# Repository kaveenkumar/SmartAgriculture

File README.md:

# SmartAgriculture
Bachelor’s final year project, 2014.

## Control of waterflow to irrigation lands from a central system using wireless communication.
Currently deployed at the institute, BMS College of Engineering, Bangalore

### Reference
https://www.researchgate.net/project/Smart-Agriculture-13

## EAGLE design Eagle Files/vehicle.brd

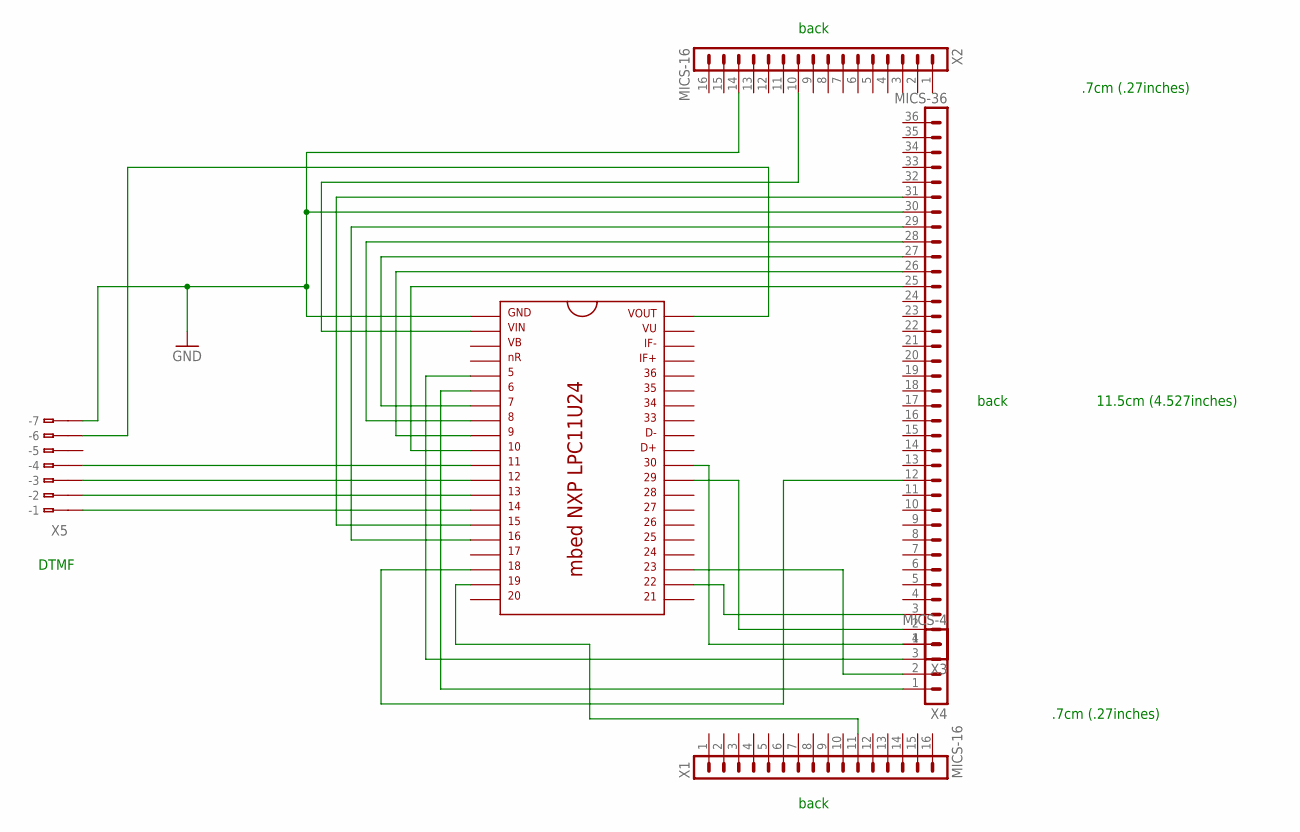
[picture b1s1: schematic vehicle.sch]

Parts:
IC1: MBED-NXP-LPC11U24; DIL40_0.9
X1, X2: MICS-16
X3: MICS-36
X4: MICS-4
X5: 233-107

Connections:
GND: IC1.1, X2.14, X3.30, X5.B7 (B-7)
unnamed: IC1.18, X3.12
unnamed: IC1.22, X3.3
unnamed: IC1.2, X2.10
unnamed: IC1.15, X3.31
unnamed: IC1.30, X3.1, X4.4
unnamed: IC1.16, X3.29
unnamed: IC1.8, X3.28
unnamed: IC1.7, X3.27
unnamed: IC1.9, X3.26
unnamed: IC1.10, X3.25
unnamed: IC1.29, X3.2
unnamed: IC1.5, X4.3
unnamed: IC1.23, X4.2
unnamed: IC1.6, X4.1
unnamed: IC1.19, X1.11
unnamed: IC1.40, X5.B6 (B-6)
unnamed: IC1.12, X5.B3 (B-3)
unnamed: IC1.13, X5.B2 (B-2)
unnamed: IC1.14, X5.B1 (B-1)

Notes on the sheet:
DTMF
.7cm (.27inches)
11.5cm (4.527inches)
back

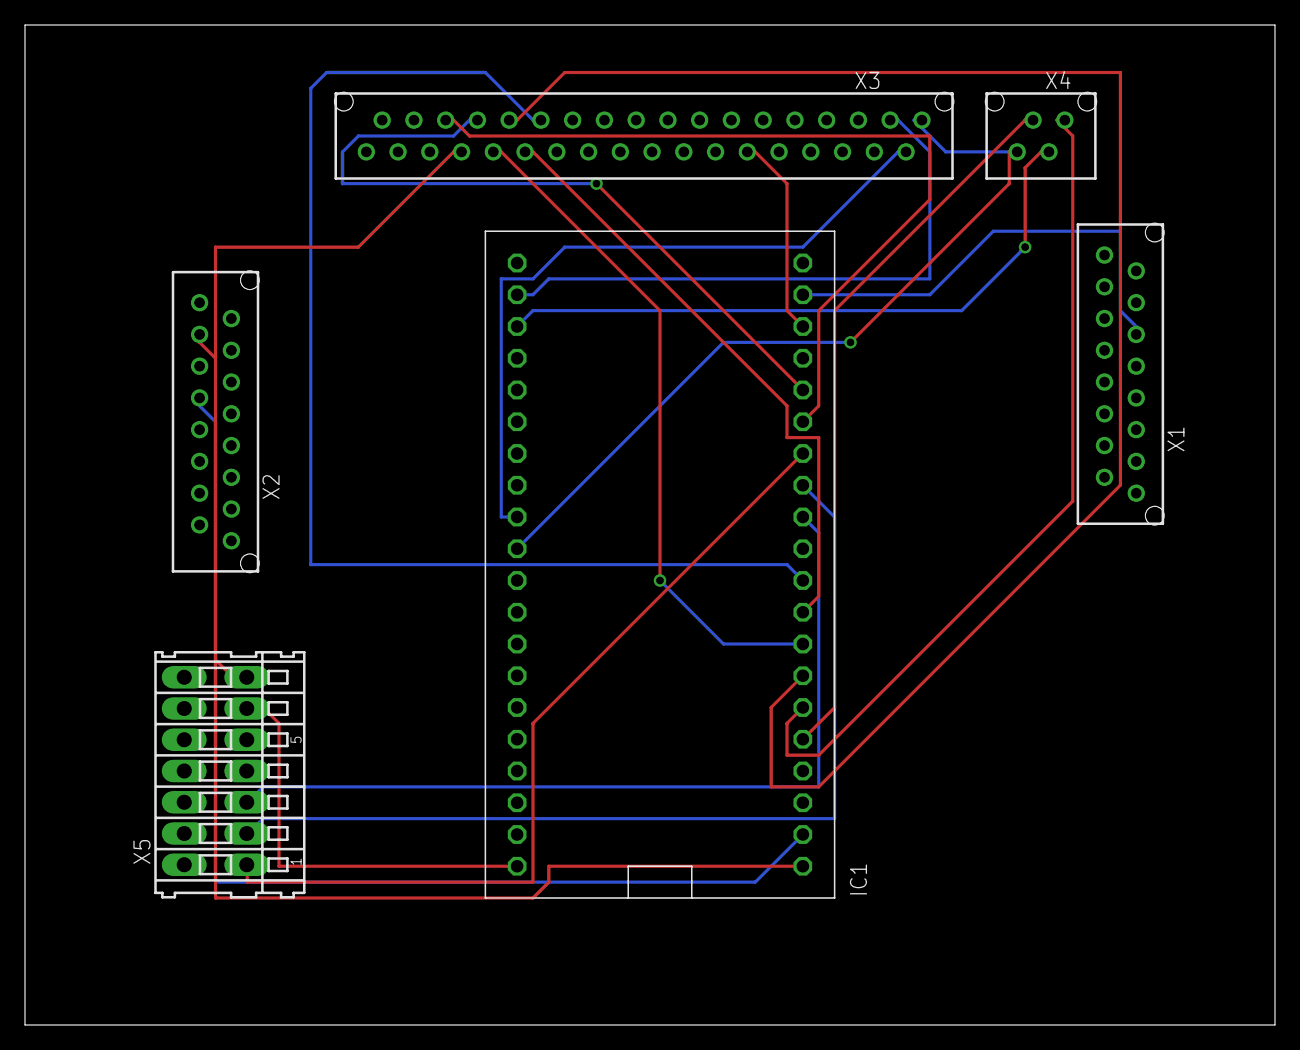
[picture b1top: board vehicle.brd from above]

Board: 2 copper layers, 100.0 x 80.0 mm, 6 parts (0 on the bottom side), 20 nets.

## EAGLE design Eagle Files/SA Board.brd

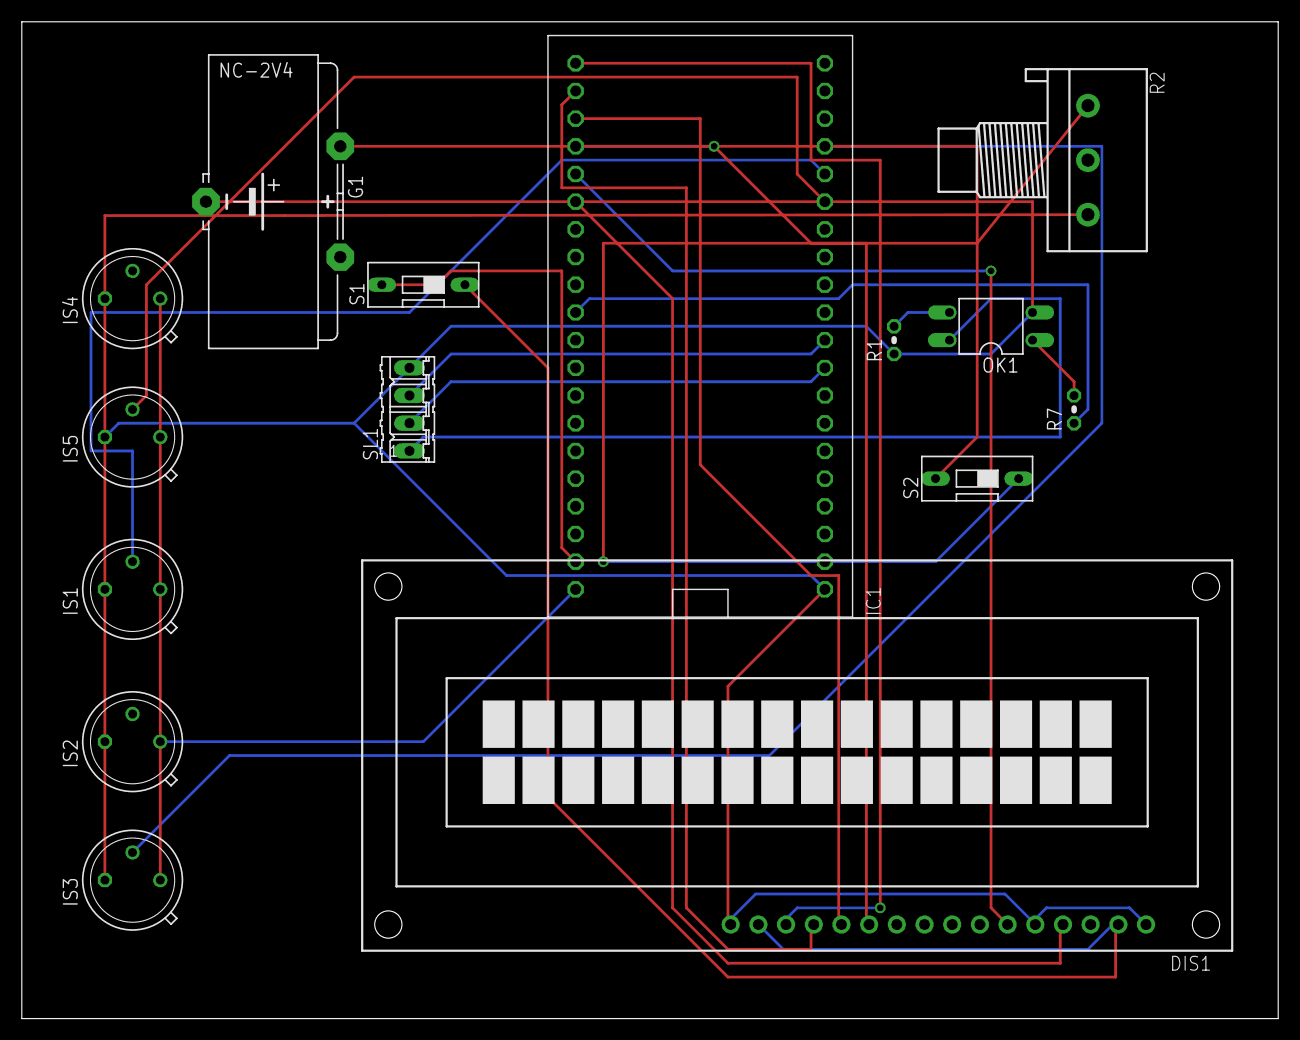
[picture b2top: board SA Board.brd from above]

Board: 2 copper layers, 115.2 x 91.4 mm, 15 parts (0 on the bottom side), 21 nets.

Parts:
DIS1: TUXGR_16X2_R2
G1: 2V110R
IC1: MBED-NXP-LPC11U24; DIL40_0.9
IS1, IS2, IS3, IS4, IS5: LME-346-F; TO39
OK1: PC817; DIL04
R1, R7: 0204V
R2: 3RP/1610N
S1, S2: DS-01
SL1: 04P

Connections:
5V: DIS1.2, DIS1.15, S1.1
+5V: OK1.4, SL1.1
GND: DIS1.1, DIS1.5, DIS1.16, G1.-, IC1.1, IS1.3, IS2.3, IS3.3, IS4.3, IS5.3, OK1.2, R1.1, R2.3, SL1.4
unnamed: OK1.3, R1.2
unnamed: IC1.15, IS5.2
unnamed: IC1.39, S1.2
unnamed: DIS1.14, IC1.21
unnamed: DIS1.13, IC1.22
unnamed: DIS1.12, IC1.23
unnamed: DIS1.11, IC1.24
unnamed: DIS1.6, IC1.25
unnamed: DIS1.4, IC1.26
unnamed: IC1.9, SL1.2
unnamed: IC1.16, IS1.2
unnamed: IC1.17, IS3.2
unnamed: IC1.10, SL1.3
unnamed: IC1.40, IS1.1, IS2.1, IS3.1, IS4.1, IS5.1
unnamed: IC1.2, R2.1, S2.1
unnamed: G1.+, S2.2
unnamed: IC1.30, R7.1
unnamed: OK1.1, R7.2
